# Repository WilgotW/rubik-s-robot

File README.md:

*Rubiks Cube Robot*

The purpose of this robot is to be able to scan, calculate solution and solve a rubiks cube. The robot has several different parts that interconnect: 
Mechanical (Robot Arm, color sensor, servos), 
Electronics (Custom made PCB with a STM32 chip), 
programming (Both computer program for solving the Rubiks cube as well as C programming for the STM32 IC)

This projects has divided all the files into sorted folders for each part of the robot told above. 

**Images**

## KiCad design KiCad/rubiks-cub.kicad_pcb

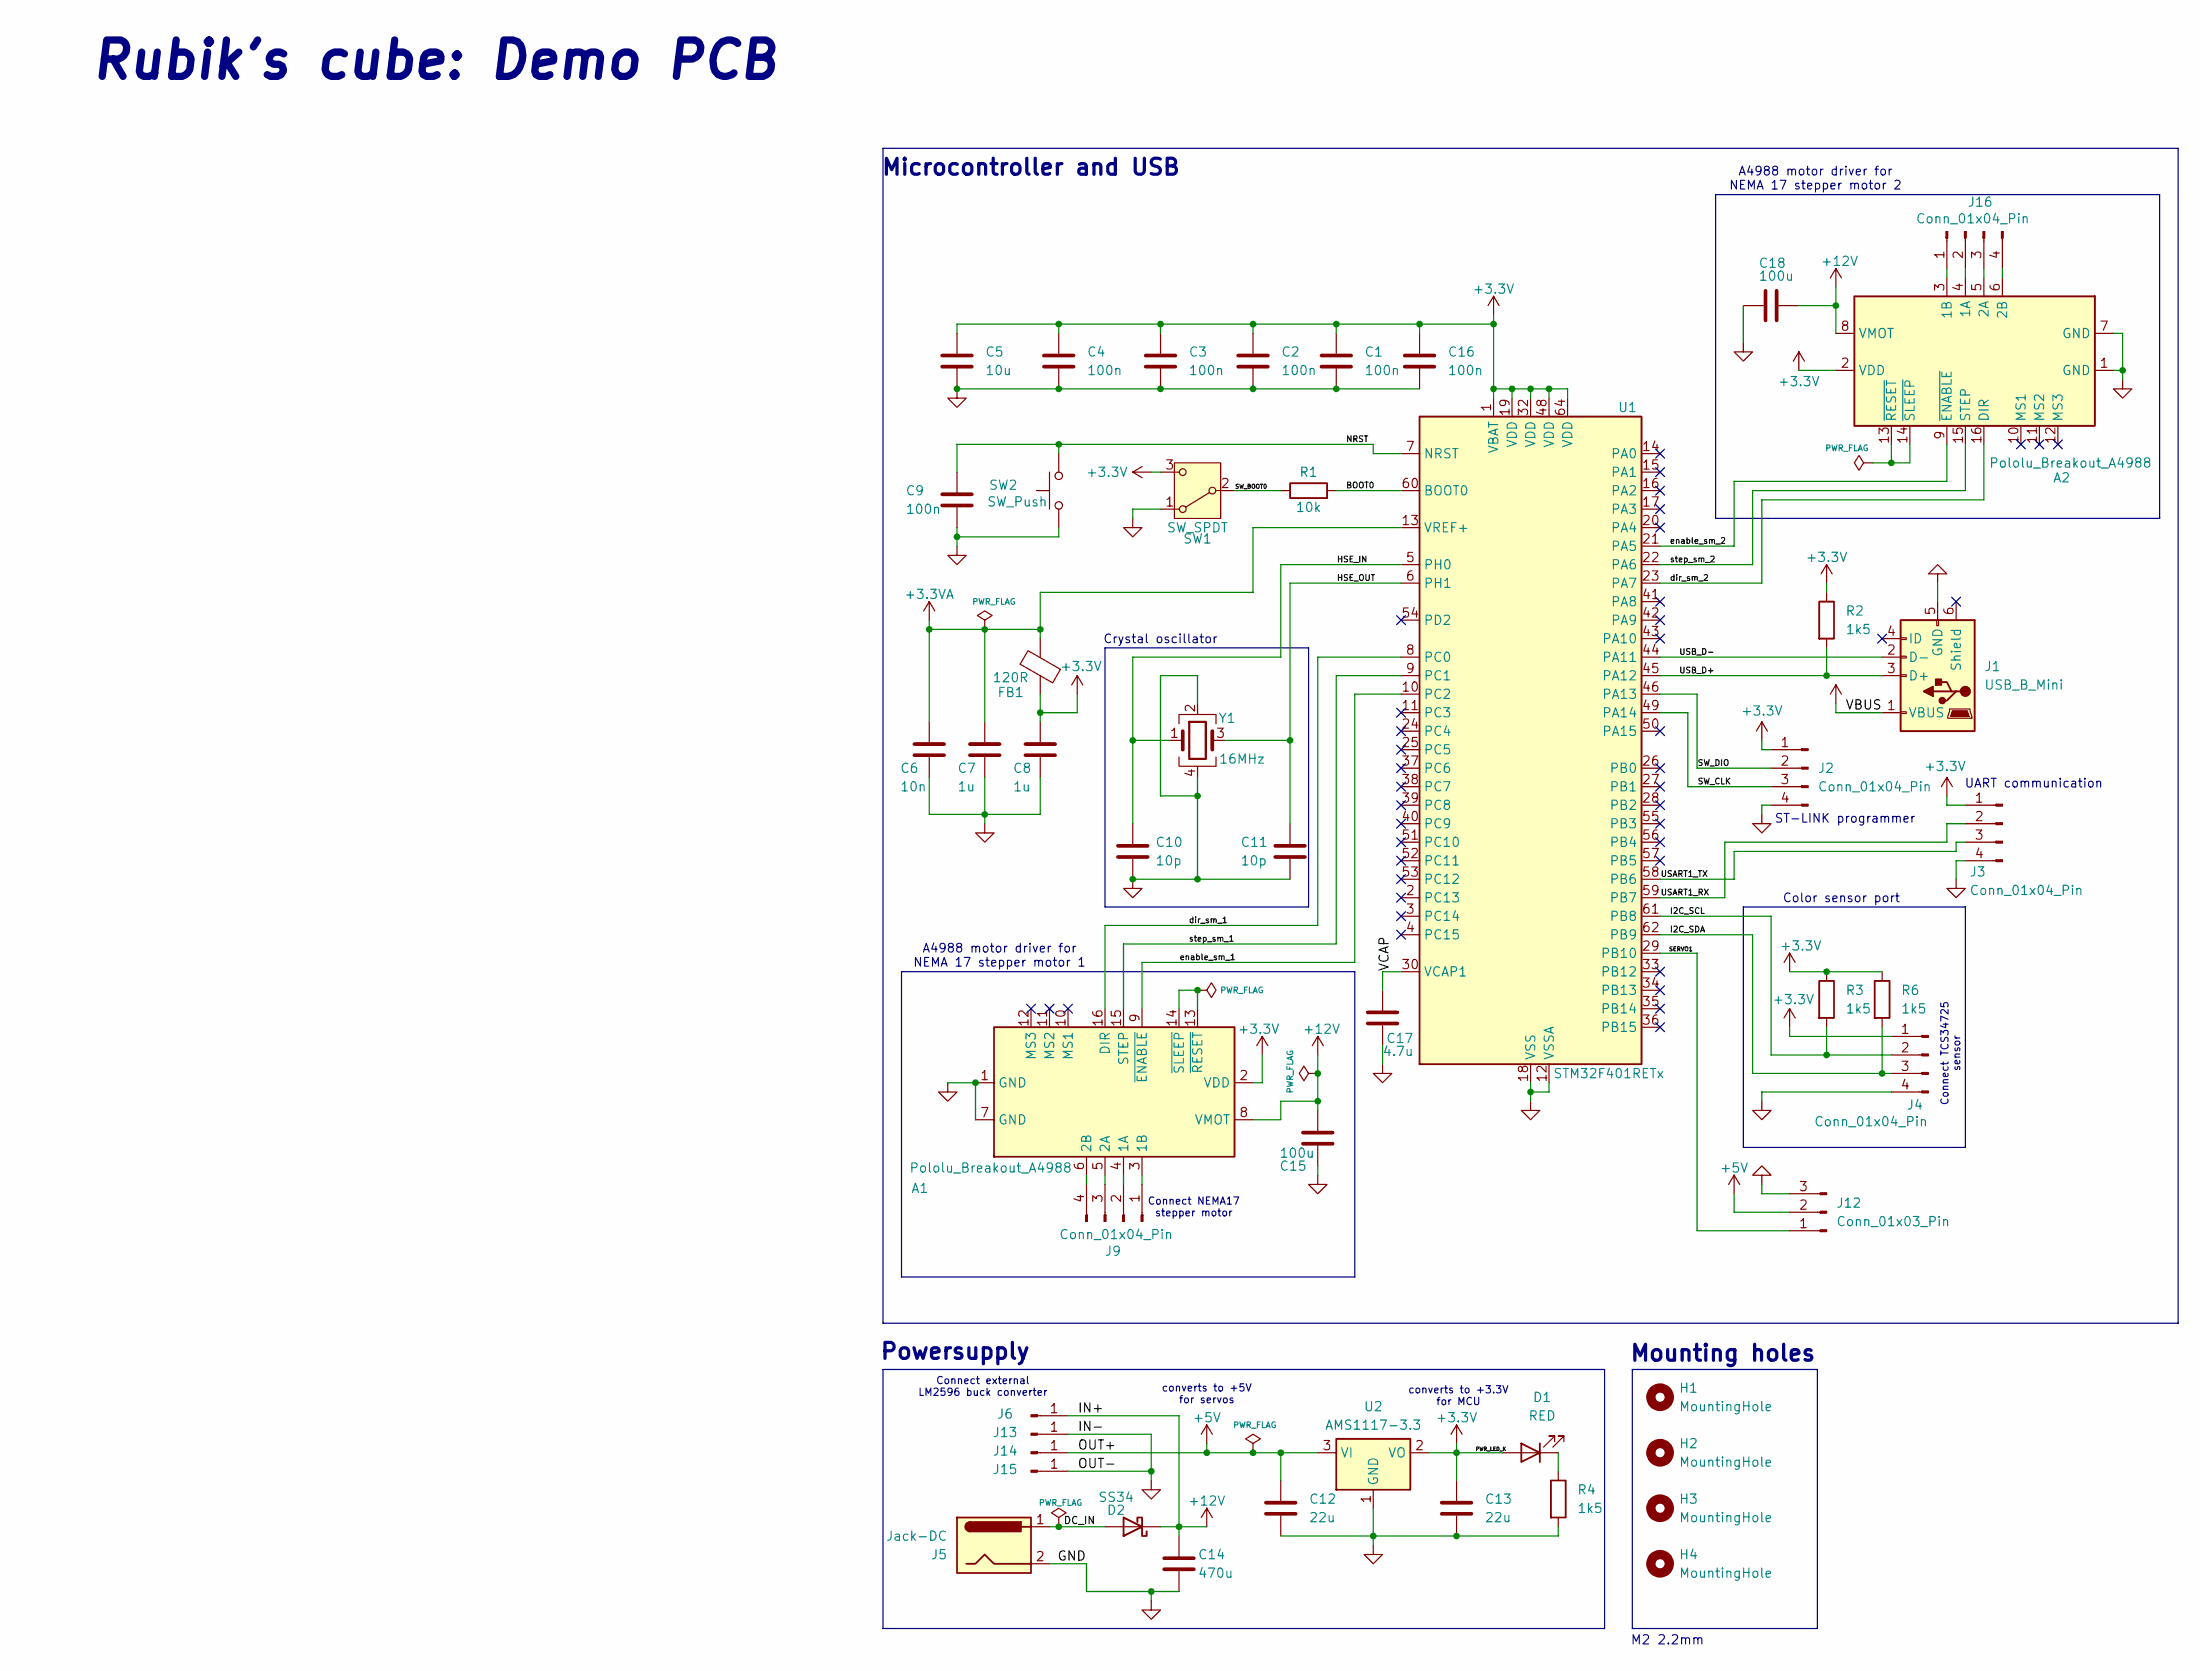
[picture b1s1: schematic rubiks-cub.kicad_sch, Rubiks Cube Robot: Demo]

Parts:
A1, A2: Pololu_Breakout_A4988; Pololu_Breakout-16_15.2x20.3mm
C1, C2, C3, C4, C9, C16: 100n; C_0402_1005Metric
C5: 10u; C_0603_1608Metric
C6: 10n; C_0402_1005Metric
C7, C8: 1u; C_0402_1005Metric
C10, C11: 10p; C_0402_1005Metric
C12, C13: 22u; C_0805_2012Metric
C14: 470u; C_Radial_D8.0mm_H7.0mm_P3.50mm
C15, C18: 100u; C_Radial_D8.0mm_H7.0mm_P3.50mm
C17: 4.7u; C_0603_1608Metric
D1: RED; LED_0603_1608Metric
D2: SS34; D_SMA
FB1: 120R; L_0603_1608Metric
H1, H2, H3, H4: MountingHole; MountingHole_2.2mm_M2
J1: USB_B_Mini; USB_Mini-B_Wuerth_65100516121_Horizontal
J2, J3, J4, J9, J16: Conn_01x04_Pin; PinHeader_1x04_P1.00mm_Vertical
J5: Jack-DC; BarrelJack_Horizontal
J6, J13, J14, J15: Conn_01x01_Pin; PinHeader_1x01_P2.54mm_Vertical
J12: Conn_01x03_Pin; PinHeader_1x03_P1.00mm_Vertical
R1: 10k; R_0402_1005Metric
R2, R3, R4, R6: 1k5; R_0402_1005Metric
SW1: SW_SPDT; SW_SPDT_PCM12
SW2: SW_Push; SW_PUSH_6mm
U1: STM32F401RETx; LQFP-64_10x10mm_P0.5mm
U2: AMS1117-3.3; SOT-223-3_TabPin2
Y1: 16MHz; Crystal_SMD_3225-4Pin_3.2x2.5mm

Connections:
+3.3V: A1.2 (VDD), A2.2 (VDD), C1.1, C2.1, C3.1, C4.1, C5.1, C8.1, C13.1, C16.1, D1.2 (A), FB1.1, J2.1, J3.1, J4.1, R2.1, R3.1, R6.1, SW1.3 (C), U1.1 (VBAT), U1.19 (VDD), U1.32 (VDD), U1.48 (VDD), U1.64 (VDD), U2.2 (VO)
+3.3VA: C6.1, C7.1, FB1.2, U1.13 (VREF+)
+5V: C12.1, J12.2, J14.1, U2.3 (VI)
+12V: A1.8 (VMOT), A2.8 (VMOT), C14.1, C15.2, C18.2, D2.1 (K), J6.1
/BOOT0: R1.2, U1.60 (BOOT0)
/DC_IN: D2.2 (A), J5.1
/HSE_IN: C10.1, U1.5 (PH0), Y1.1
/HSE_OUT: C11.1, U1.6 (PH1), Y1.3
/I2C_SCL: J4.2, R3.2, U1.61 (PB8)
/I2C_SDA: J4.3, R6.2, U1.62 (PB9)
/NRST: C9.1, SW2.2, U1.7 (NRST)
/SERVO1: J12.1, U1.29 (PB10)
/SW_BOOT0: R1.1, SW1.2 (B)
/SW_CLK: J2.3, U1.49 (PA14)
/SW_DIO: J2.2, U1.46 (PA13)
/USART1_RX: J3.2, U1.59 (PB7)
/USART1_TX: J3.3, U1.58 (PB6)
/USB_D+: J1.3 (D+), R2.2, U1.45 (PA12)
/USB_D-: J1.2 (D-), U1.44 (PA11)
/VCAP: C17.1, U1.30 (VCAP1)
/dir_sm_1: A1.16 (DIR), U1.8 (PC0)
/dir_sm_2: A2.16 (DIR), U1.23 (PA7)
/enable_sm_1: A1.9 (~ENABLE), U1.10 (PC2)
/enable_sm_2: A2.9 (~ENABLE), U1.21 (PA5)
/step_sm_1: A1.15 (STEP), U1.9 (PC1)
/step_sm_2: A2.15 (STEP), U1.22 (PA6)
GND: A1.1 (GND), A1.7 (GND), A2.1 (GND), A2.7 (GND), C1.2, C2.2, C3.2, C4.2, C5.2, C6.2, C7.2, C8.2, C9.2, C10.2, C11.2, C12.2, C13.2, C14.2, C15.1, C16.2, C17.2, C18.1, J1.5 (GND), J2.4, J3.4, J4.4, J5.2, J12.3, J13.1, J15.1, R4.2, SW1.1 (A), SW2.1, U1.12 (VSSA), U1.18 (VSS), U1.31 (VSS), U1.47 (VSS), U1.63 (VSS), U2.1 (GND), Y1.2, Y1.4
unnamed: A1.4 (1A), J9.2
unnamed: A1.3 (1B), J9.1
unnamed: A1.5 (2A), J9.3
unnamed: A1.6 (2B), J9.4
unnamed: A1.13 (~RESET), A1.14 (~SLEEP)
unnamed: A2.4 (1A), J16.2
unnamed: A2.3 (1B), J16.1
unnamed: A2.5 (2A), J16.3
unnamed: A2.6 (2B), J16.4
unnamed: A2.13 (~RESET), A2.14 (~SLEEP)
unnamed: D1.1 (K), R4.1
VBUS: J1.1 (VBUS)

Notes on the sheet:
Powersupply
Mounting holes
converts to +3.3V for MCU
Crystal oscillator
Connect TCS34725 sensor
ST-LINK programmer
Color sensor port
converts to +5V for servos
A4988 motor driver for NEMA 17 stepper motor 1
A4988 motor driver for NEMA 17 stepper motor 2
Connect external LM2596 buck converter
M2 2.2mm
UART communication
Rubik's cube: Demo PCB
Microcontroller and USB
Connect NEMA17 stepper motor

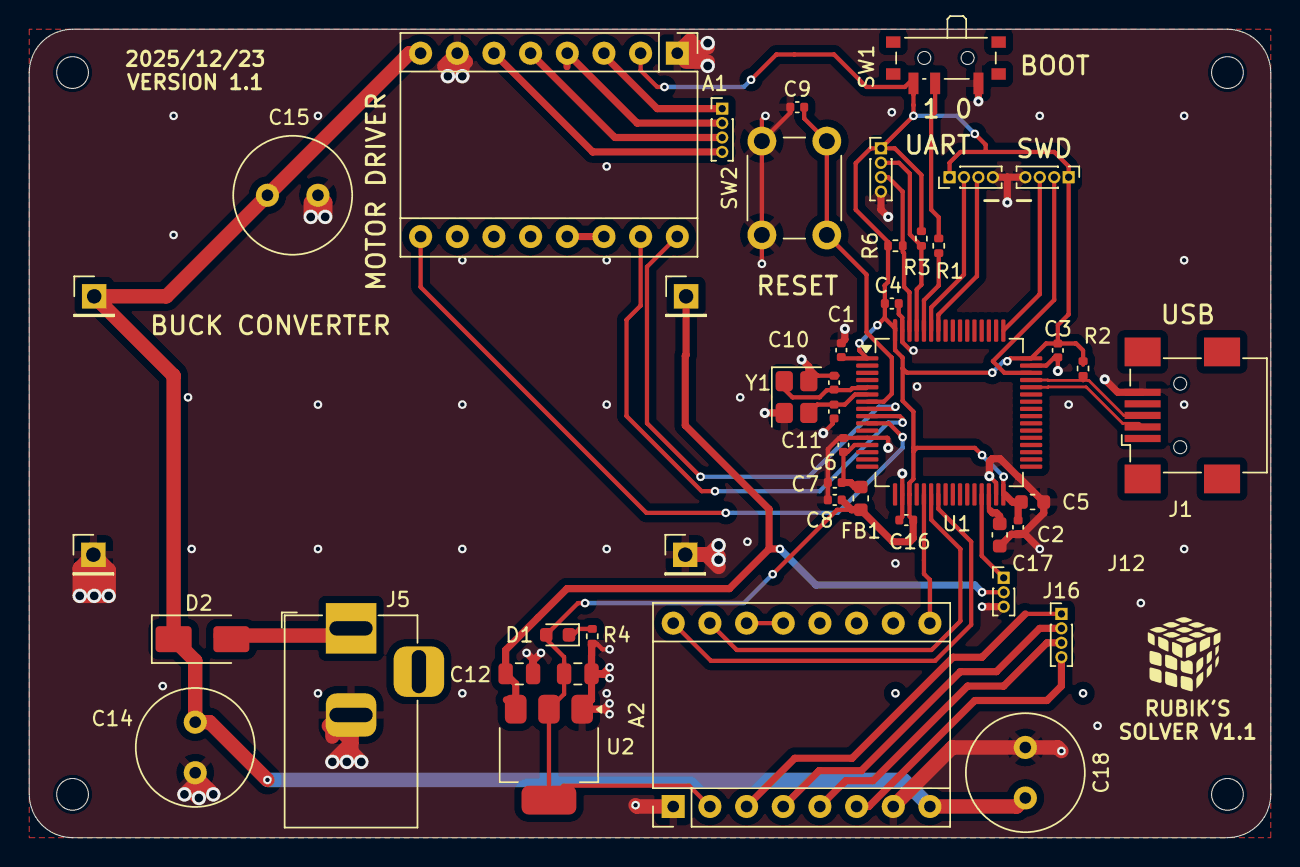
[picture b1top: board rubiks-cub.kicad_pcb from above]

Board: 2 copper layers, 86.0 x 56.0 mm, 49 parts (0 on the bottom side), 38 nets.

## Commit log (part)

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2025-11-26 KiCad
2025-11-27 power regulator
2025-11-27 demo pcb schematic done
2025-11-29 added extra components
2025-11-29 schematic done
2025-11-29 fixed errors
2025-12-02 pcb design
2025-12-03 models
2025-12-22 pcb progress
2026-02-21 added bare-metal project
2026-06-09 UART working
2026-06-30 driver setup
